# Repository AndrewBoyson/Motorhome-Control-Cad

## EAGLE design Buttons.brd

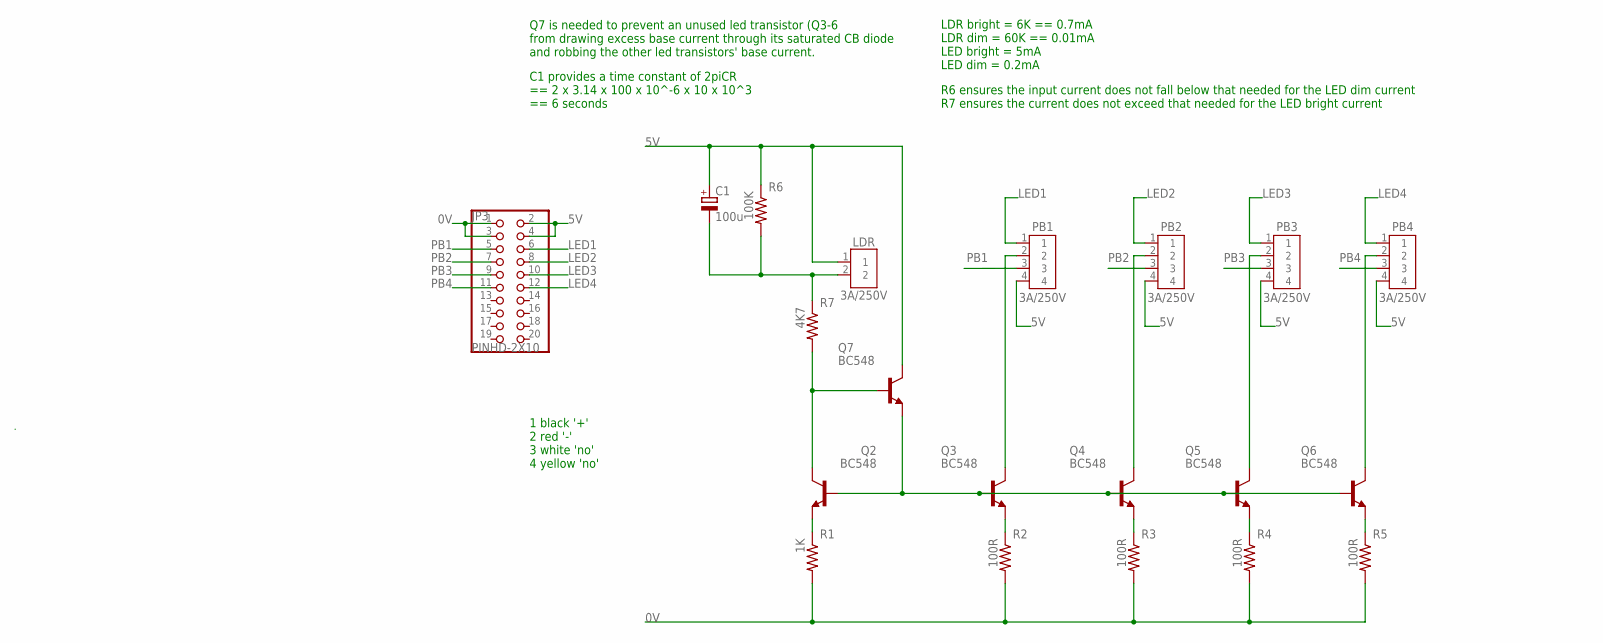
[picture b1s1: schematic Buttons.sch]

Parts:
C1: 100u; E3,5-8
JP3: PINHD-2X10; 2X10
LDR: 3A/250V; B2B-XH-A
PB1, PB2, PB3, PB4: 3A/250V; B4B-XH-A
Q2, Q3, Q4, Q5, Q6, Q7: BC548; TO92-EBC
R1: 1K; 0204/7
R2, R3, R4, R5: 100R; 0204/7
R6: 100K; 0204/7
R7: 4K7; 0204/7

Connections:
0V: JP3.1, JP3.3, R1.2, R2.2, R3.2, R4.2, R5.2
5V: C1.+, JP3.2, JP3.4, LDR.1, PB1.4, PB2.4, PB3.4, PB4.4, Q7.C, R6.1
LED1: JP3.6, PB1.1
LED2: JP3.8, PB2.1
LED3: JP3.10, PB3.1
LED4: JP3.12, PB4.1
unnamed: Q2.B, Q3.B, Q4.B, Q5.B, Q6.B, Q7.E
unnamed: C1.-, LDR.2, R6.2, R7.1
unnamed: Q2.C, Q7.B, R7.2
unnamed: Q2.E, R1.1
unnamed: Q3.E, R2.1
unnamed: Q4.E, R3.1
unnamed: Q5.E, R4.1
unnamed: Q6.E, R5.1
unnamed: PB1.2, Q3.C
unnamed: PB2.2, Q4.C
unnamed: PB3.2, Q5.C
unnamed: PB4.2, Q6.C
PB1: JP3.5, PB1.3
PB2: JP3.7, PB2.3
PB3: JP3.9, PB3.3
PB4: JP3.11, PB4.3

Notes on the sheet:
Q7 is needed to prevent an unused led transistor (Q3-6 from drawing excess base current through its saturated CB diode and robbing the other led transistors' base current.
C1 provides a time constant of 2piCR == 2 x 3.14 x 100 x 10^-6 x 10 x 10^3 == 6 seconds
LDR bright = 6K == 0.7mA LDR dim = 60K == 0.01mA LED bright = 5mA LED dim = 0.2mA
R6 ensures the input current does not fall below that needed for the LED dim current R7 ensures the current does not exceed that needed for the LED bright current
1 black '+' 2 red '-' 3 white 'no' 4 yellow 'no'

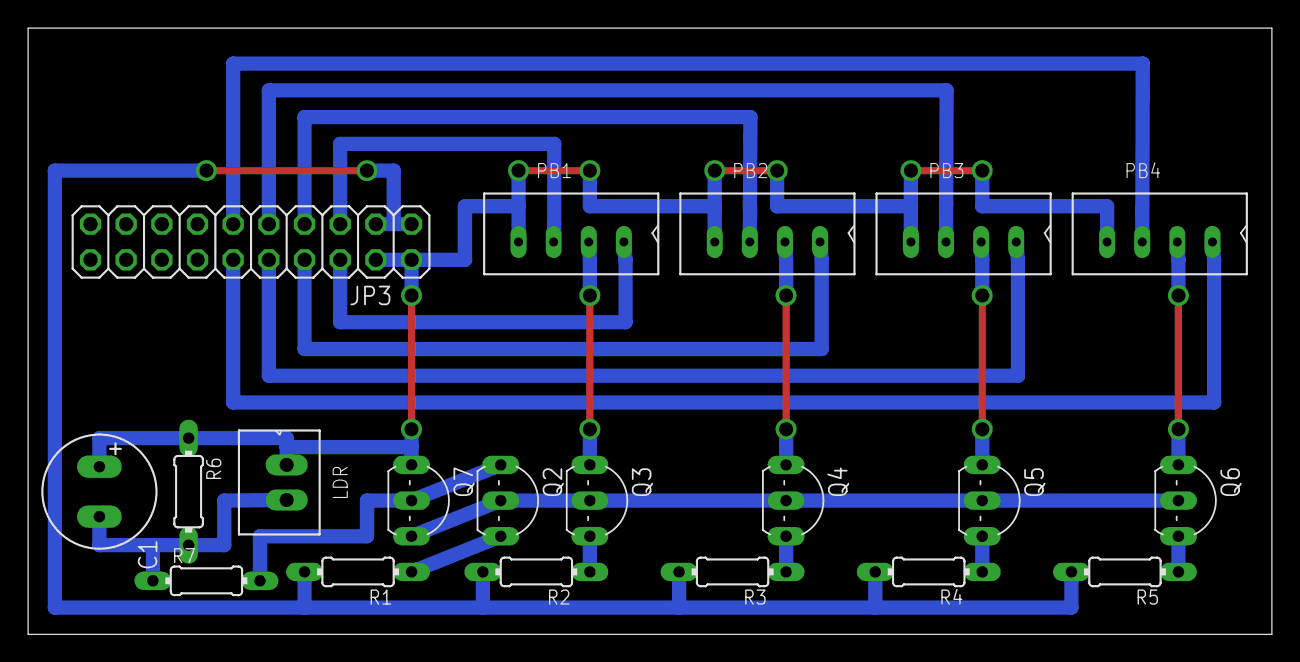
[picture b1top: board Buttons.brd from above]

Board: 2 copper layers, 88.6 x 43.2 mm, 20 parts (0 on the bottom side), 22 nets.

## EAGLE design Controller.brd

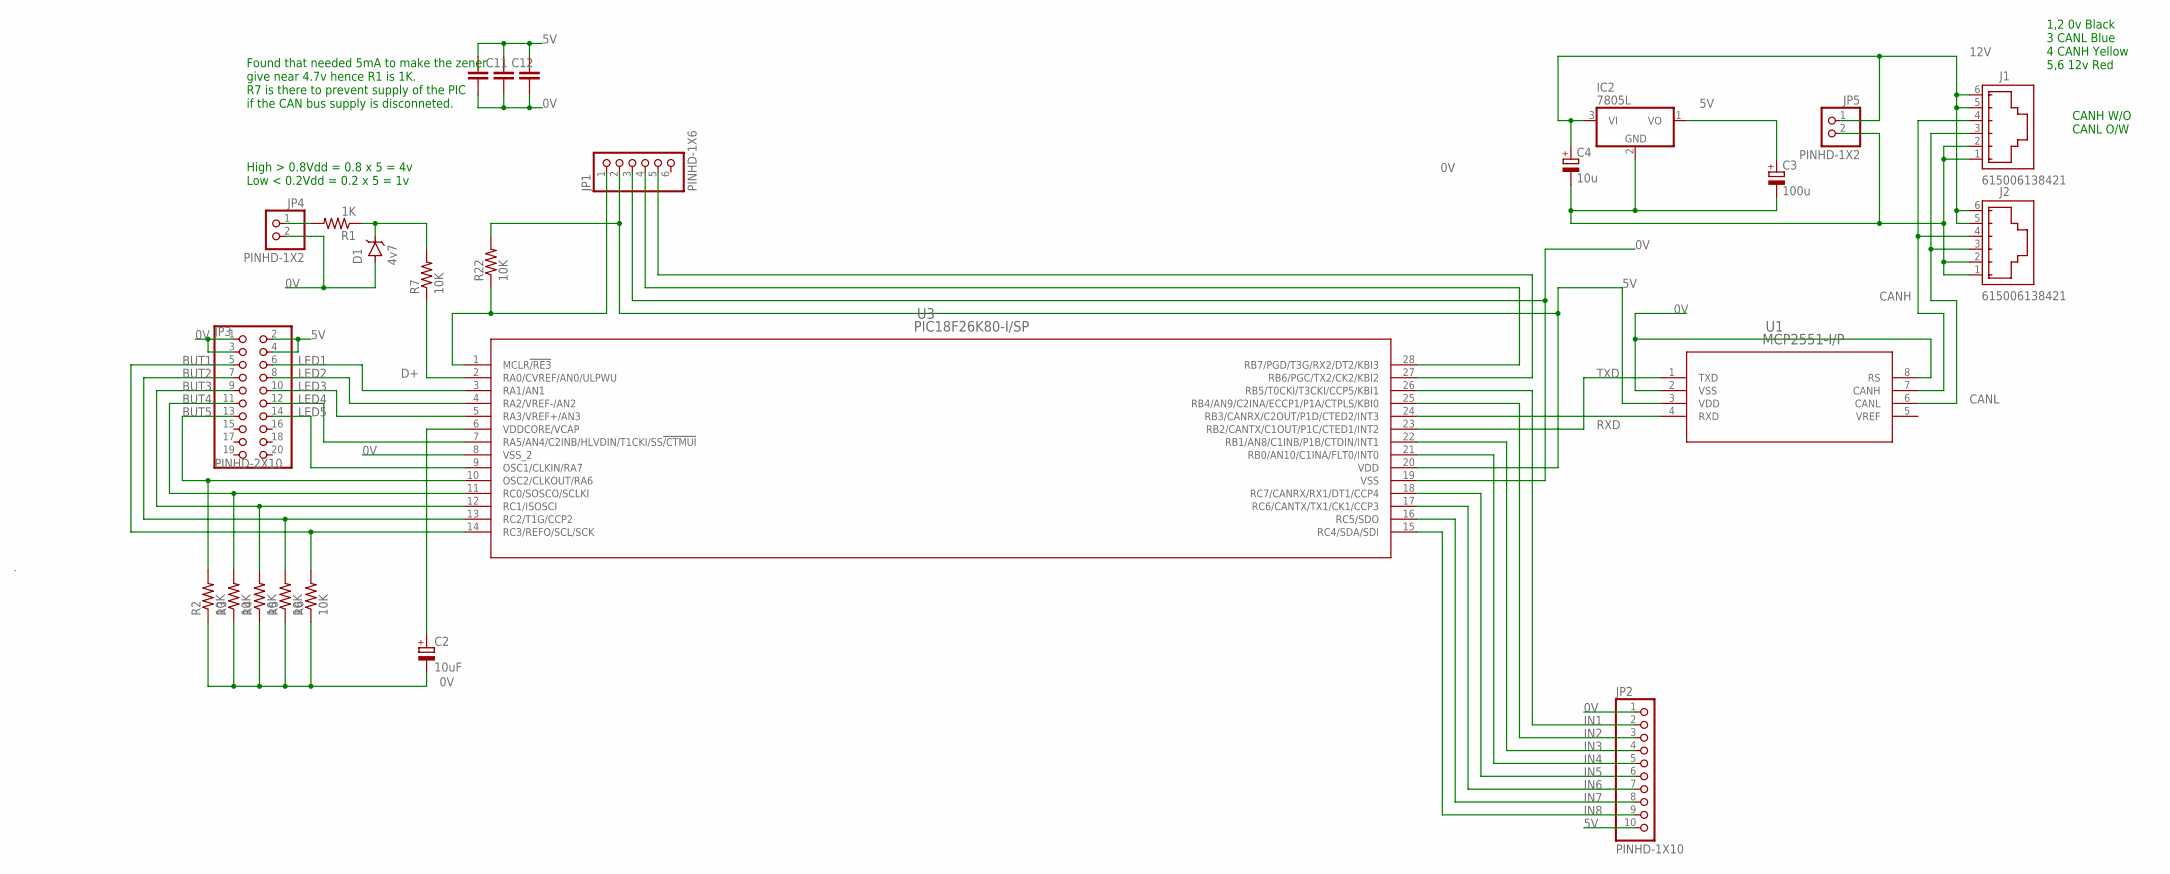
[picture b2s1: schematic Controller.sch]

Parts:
C2: 10uF; E3,5-8
C3: 100u; E3,5-8
C4: 10u; E3,5-8
C7, C11, C12: C2,5-3; C2.5-3
D1: 4v7; DO-35
IC2: 7805L; TO92
J1, J2: 615006138421
JP1: PINHD-1X6; 1X06
JP2: PINHD-1X10; 1X10
JP3: PINHD-2X10; 2X10
JP4, JP5: PINHD-1X2; 1X02
R1: 1K; 0204/7
R2, R3, R4, R5, R6, R7, R22: 10K; 0204/7
U1: MCP2551-I/P; PDIP8_300MC_MCH
U3: PIC18F26K80-I/SP; SPDIP28_300MC_MCH

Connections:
0V: C2.-, C3.-, C4.-, C7.2, C11.2, C12.2, D1.A, IC2.2 (GND), J1.1, J1.2, J2.1, J2.2, JP1.3, JP2.1, JP3.1, JP3.3, JP4.2, JP5.2, R2.1, R3.1, R4.1, R5.1, R6.1, U1.2 (VSS), U1.8 (RS), U3.8 (VSS_2), U3.19 (VSS)
5V: C3.+, C7.1, C11.1, C12.1, IC2.1 (VO), JP1.2, JP2.10, JP3.2, JP3.4, R22.2, U1.3 (VDD), U3.20 (VDD)
12V: C4.+, IC2.3 (VI), J1.5, J1.6, J2.5, J2.6, JP5.1
BUT1: JP3.5, R6.2, U3.14 (RC3/REFO/SCL/SCK)
BUT2: JP3.7, R5.2, U3.13 (RC2/T1G/CCP2)
BUT3: JP3.9, R4.2, U3.12 (RC1/ISOSCI)
BUT4: JP3.11, R3.2, U3.11 (RC0/SOSCO/SCLKI)
BUT5: JP3.13, R2.2, U3.10 (OSC2/CLKOUT/RA6)
CANH: J1.4, J2.4, U1.7 (CANH)
CANL: J1.3, J2.3, U1.6 (CANL)
D+: R7.1, U3.2 (RA0/CVREF/AN0/ULPWU)
IN1: JP2.2, U3.26 (RB5/T0CKI/T3CKI/CCP5/KBI1)
IN2: JP2.3, U3.25 (RB4/AN9/C2INA/ECCP1/P1A/CTPLS/KBI0)
IN3: JP2.4, U3.22 (RB1/AN8/C1INB/P1B/CTDIN/INT1)
IN4: JP2.5, U3.21 (RB0/AN10/C1INA/FLT0/INT0)
IN5: JP2.6, U3.18 (RC7/CANRX/RX1/DT1/CCP4)
IN6: JP2.7, U3.17 (RC6/CANTX/TX1/CK1/CCP3)
IN7: JP2.8, U3.16 (RC5/SDO)
IN8: JP2.9, U3.15 (RC4/SDA/SDI)
LED1: JP3.6, U3.3 (RA1/AN1)
LED2: JP3.8, U3.4 (RA2/VREF-/AN2)
LED3: JP3.10, U3.5 (RA3/VREF+/AN3)
LED4: JP3.12, U3.7 (RA5/AN4/C2INB/HLVDIN/T1CKI/SS!/CTMUI)
LED5: JP3.14, U3.9 (OSC1/CLKIN/RA7)
unnamed: D1.C, R1.1, R7.2
unnamed: JP1.1, R22.1, U3.1 (MCLR!/RE3)
unnamed: JP1.4, U3.28 (RB7/PGD/T3G/RX2/DT2/KBI3)
unnamed: JP1.5, U3.27 (RB6/PGC/TX2/CK2/KBI2)
unnamed: C2.+, U3.6 (VDDCORE/VCAP)
unnamed: JP4.1, R1.2
RXD: U1.4 (RXD), U3.24 (RB3/CANRX/C2OUT/P1D/CTED2/INT3)
TXD: U1.1 (TXD), U3.23 (RB2/CANTX/C1OUT/P1C/CTED1/INT2)

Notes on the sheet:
CANH W/O CANL O/W
High > 0.8Vdd = 0.8 x 5 = 4v Low < 0.2Vdd = 0.2 x 5 = 1v
1,2 0v Black 3 CANL Blue 4 CANH Yellow 5,6 12v Red
Found that needed 5mA to make the zener give near 4.7v hence R1 is 1K. R7 is there to prevent supply of the PIC if the CAN bus supply is disconneted.

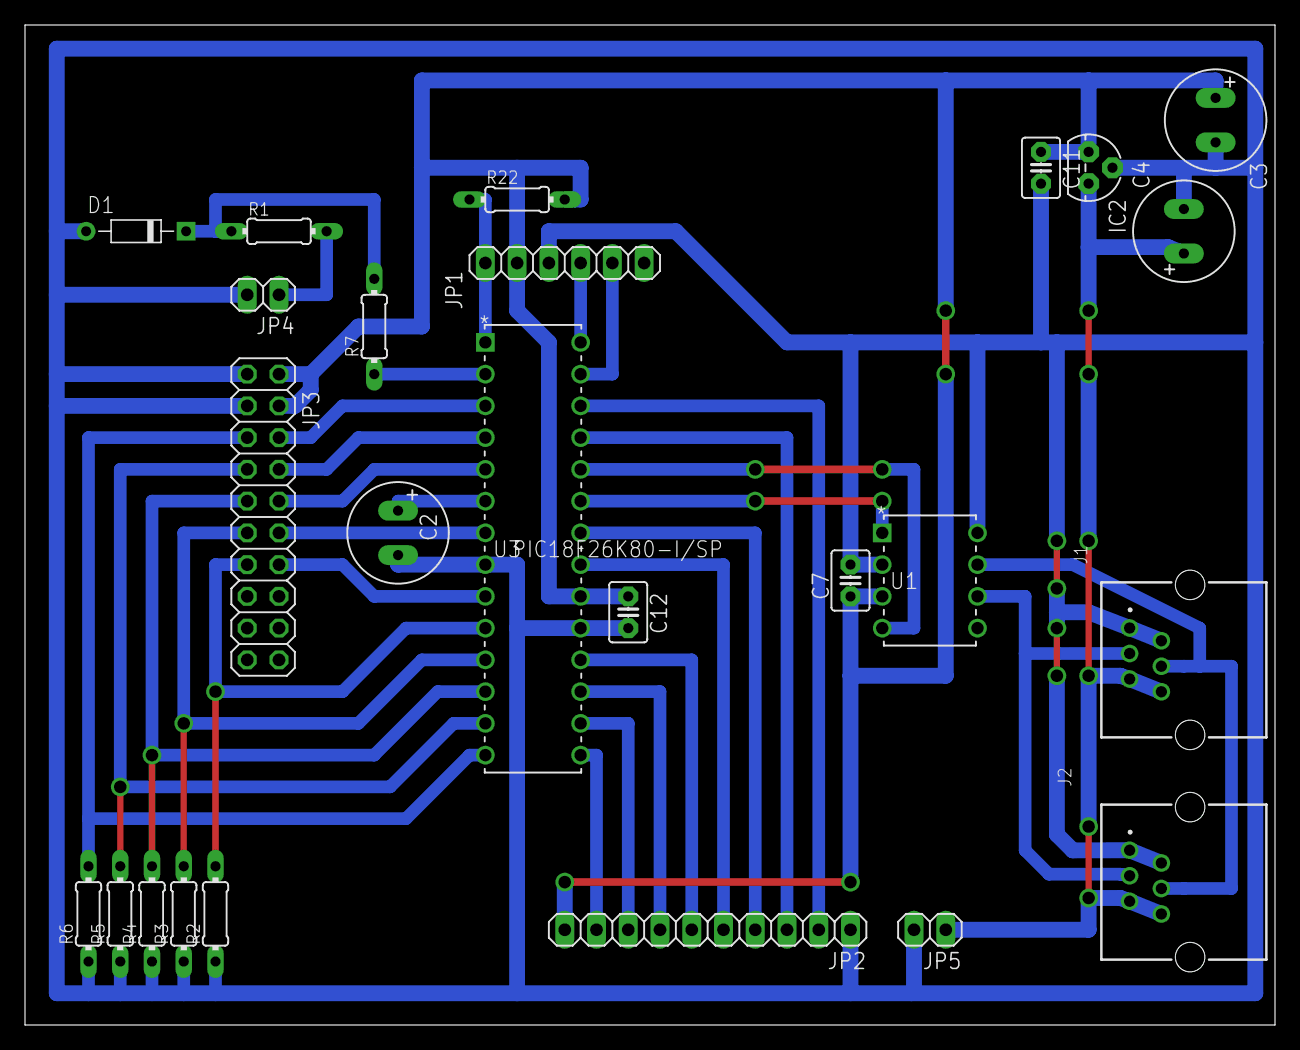
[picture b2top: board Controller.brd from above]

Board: 2 copper layers, 100.0 x 80.0 mm, 25 parts (0 on the bottom side), 32 nets.

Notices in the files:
parts and their libraries:
Wurth_Connectors_WR-MJ: Copyright: Würth Elektronik
COPYRIGHT: Copyright (C) 2021 Ultra Librarian. All rights reserved.
